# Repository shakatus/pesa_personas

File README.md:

# pesa_personas
Basculas pesa personas

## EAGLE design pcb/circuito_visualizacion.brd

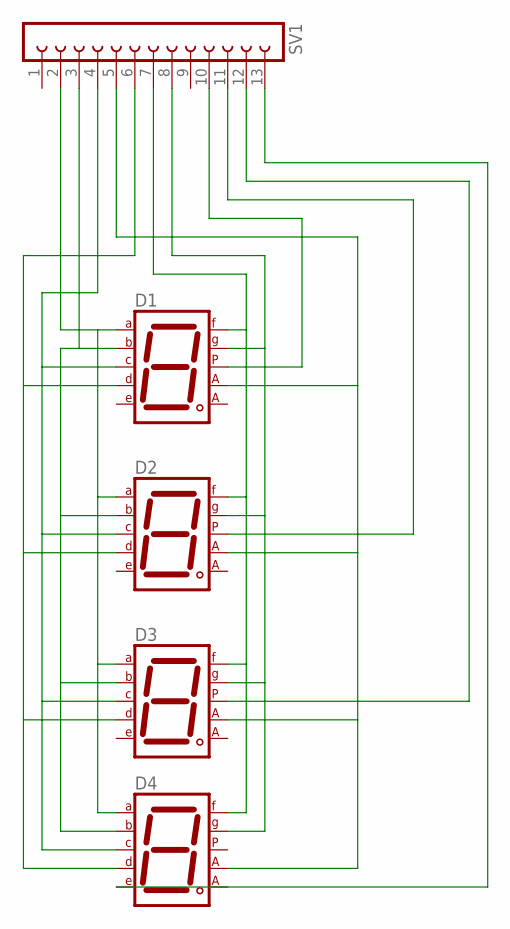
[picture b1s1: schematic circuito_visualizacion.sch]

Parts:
D1, D2, D3, D4: 7SEG-CA; 7SEG-13
SV1: FE13-1; FE13

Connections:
unnamed: D3.5 (DP), SV1.12
unnamed: D4.1 (E), SV1.13
unnamed: D1.5 (DP), SV1.10
unnamed: D1.7 (A), D2.7 (A), D3.7 (A), D4.7 (A), SV1.2
unnamed: D1.6 (B), D2.6 (B), D3.6 (B), D4.6 (B), SV1.3
unnamed: D1.4 (C), D2.4 (C), D3.4 (C), D4.4 (C), SV1.4
unnamed: D1.2 (D), D2.2 (D), D3.2 (D), D4.2 (D), SV1.6
unnamed: D1.9 (F), D2.9 (F), D3.9 (F), D4.9 (F), SV1.7
unnamed: D1.10 (G), D2.10 (G), D3.10 (G), D4.10 (G), SV1.8
unnamed: D2.5 (DP), SV1.11
unnamed: D1.3 (CA1), D2.3 (CA1), D3.3 (CA1), D4.3 (CA1), SV1.5

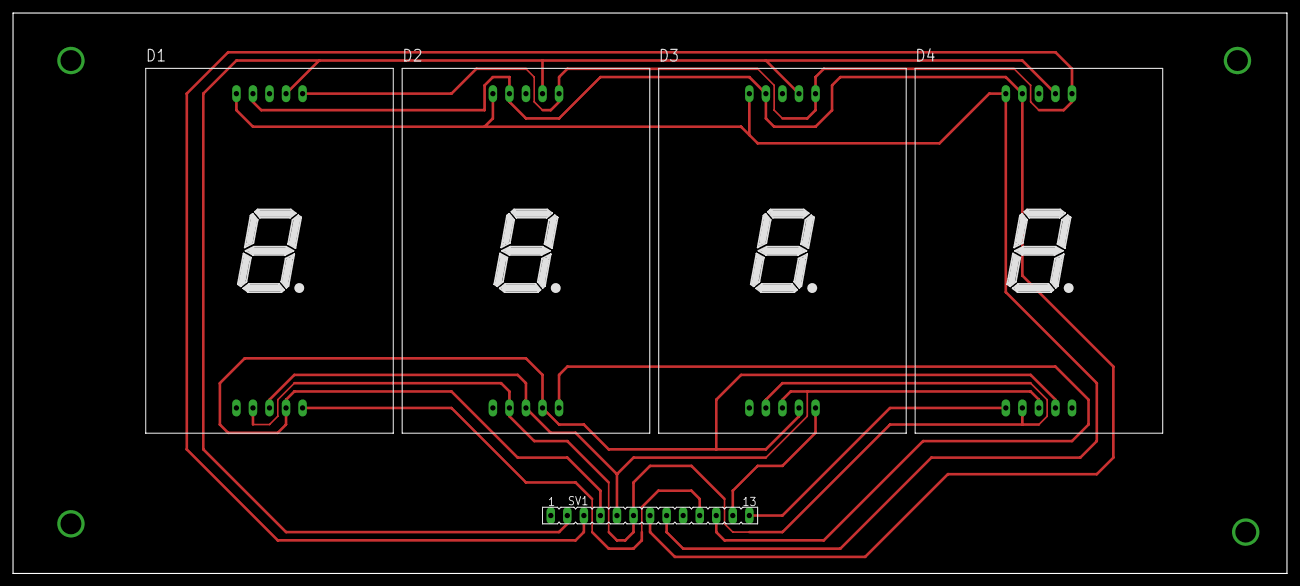
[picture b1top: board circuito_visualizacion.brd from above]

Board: 2 copper layers, 195.6 x 86.0 mm, 5 parts (0 on the bottom side), 11 nets.

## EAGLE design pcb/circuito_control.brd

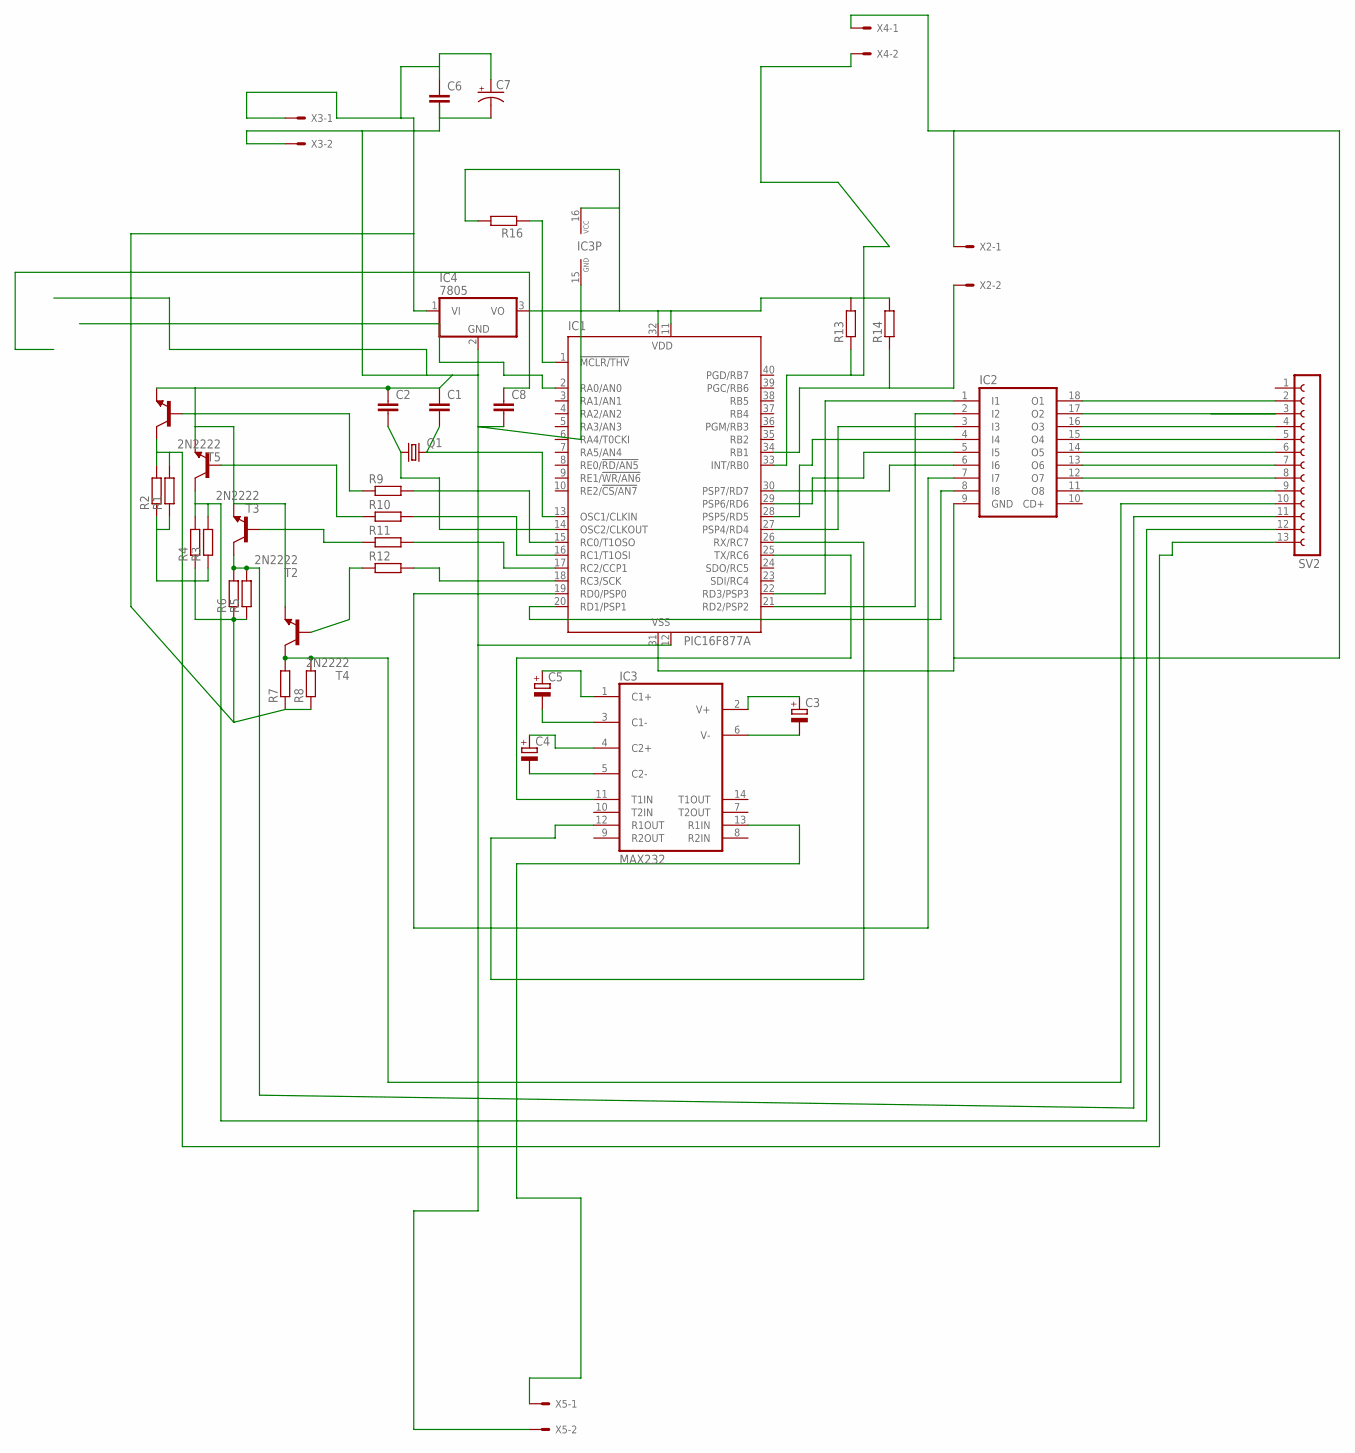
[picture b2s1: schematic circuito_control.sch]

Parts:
C1, C2, C6, C8: C-EU025-025X050; C025-025X050
C3, C4, C5: CPOL-EUE1.8-4; E1,8-4
C7: CPOL-USE5-10.5; E5-10,5
IC1: PIC16F877A; DIL40
IC2: ULN2803A; DIL18
IC3: MAX232; DIL16
IC4: 7805; TO220V
Q1: CRYSTALHC49U70; HC49U70
R1, R2, R3, R4, R5, R6, R7, R8: R-EU_0411/15; 0411/15
R9, R10, R11, R12, R13, R14, R16: R-EU_0207/7; 0207/7
SV2: FE13-1; FE13
T2, T3, T4, T5: 2N2222; TO18
X2, X3, X4, X5: KK-156-2

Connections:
unnamed: C6.1, C7.+, IC4.1 (VI), R1.1, R2.1, R3.1, R4.1, R5.1, R6.1, R7.1, R8.1, X3.1
unnamed: IC1.1 (!MCLR/THV), R16.1
unnamed: IC3.13 (R1IN), X5.1
unnamed: C3.-, IC3.6 (V-)
unnamed: C3.+, IC3.2 (V+)
unnamed: C4.+, IC3.4 (C2+)
unnamed: C4.-, IC3.5 (C2-)
unnamed: C5.-, IC3.3 (C1-)
unnamed: C5.+, IC3.1 (C1+)
unnamed: IC1.25 (TX/RC6), IC3.11 (T1IN)
unnamed: IC1.26 (RX/RC7), IC3.12 (R1OUT)
unnamed: IC1.22 (RD3/PSP3), IC2.1 (I1)
unnamed: IC1.21 (RD2/PSP2), IC2.2 (I2)
unnamed: IC1.28 (PSP5/RD5), IC2.4 (I4)
unnamed: IC1.20 (RD1/PSP1), IC2.8 (I8)
unnamed: IC1.29 (PSP6/RD6), IC2.5 (I5)
unnamed: IC1.30 (PSP7/RD7), IC2.6 (I6)
unnamed: IC1.27 (PSP4/RD4), IC2.3 (I3)
unnamed: IC1.15 (RC0/T1OSO), R9.2
unnamed: IC1.16 (RC1/T1OSI), R10.2
unnamed: IC1.17 (RC2/CCP1), R11.2
unnamed: IC1.18 (RC3/SCK), R12.2
unnamed: R9.1, T5.2 (B)
unnamed: R10.1, T3.2 (B)
unnamed: R11.1, T2.2 (B)
unnamed: R12.1, T4.2 (B)
unnamed: R7.2, R8.2, SV2.10, T4.3 (C)
unnamed: R5.2, R6.2, SV2.11, T2.3 (C)
unnamed: R3.2, R4.2, SV2.12, T3.3 (C)
unnamed: R1.2, R2.2, SV2.13, T5.3 (C)
unnamed: C2.2, IC1.14 (OSC2/CLKOUT), Q1.1
unnamed: IC2.18 (O1), SV2.2
unnamed: IC2.17 (O2), SV2.3
unnamed: IC1.34 (RB1), R14.1, X2.2
unnamed: C8.1, IC1.11 (VDD), IC1.32 (VDD), IC3.16 (VCC), IC4.3 (VO), R13.2, R14.2, R16.2
unnamed: C1.2, IC1.13 (OSC1/CLKIN), Q1.2
unnamed: IC2.16 (O3), SV2.4
unnamed: IC2.15 (O4), SV2.5
unnamed: IC2.14 (O5), SV2.6
unnamed: IC2.13 (O6), SV2.7
unnamed: IC2.12 (O7), SV2.8
unnamed: IC2.11 (O8), SV2.9
unnamed: IC1.33 (INT/RB0), R13.1, X4.2
unnamed: C1.1, C2.1, C6.2, C7.-, C8.2, IC1.12 (VSS), IC1.31 (VSS), IC2.9 (GND), IC3.15 (GND), IC4.2 (GND), T2.1 (E), T3.1 (E), T4.1 (E), T5.1 (E), X2.1, X3.2, X4.1, X5.2
unnamed: IC1.19 (RD0/PSP0), IC2.7 (I7)

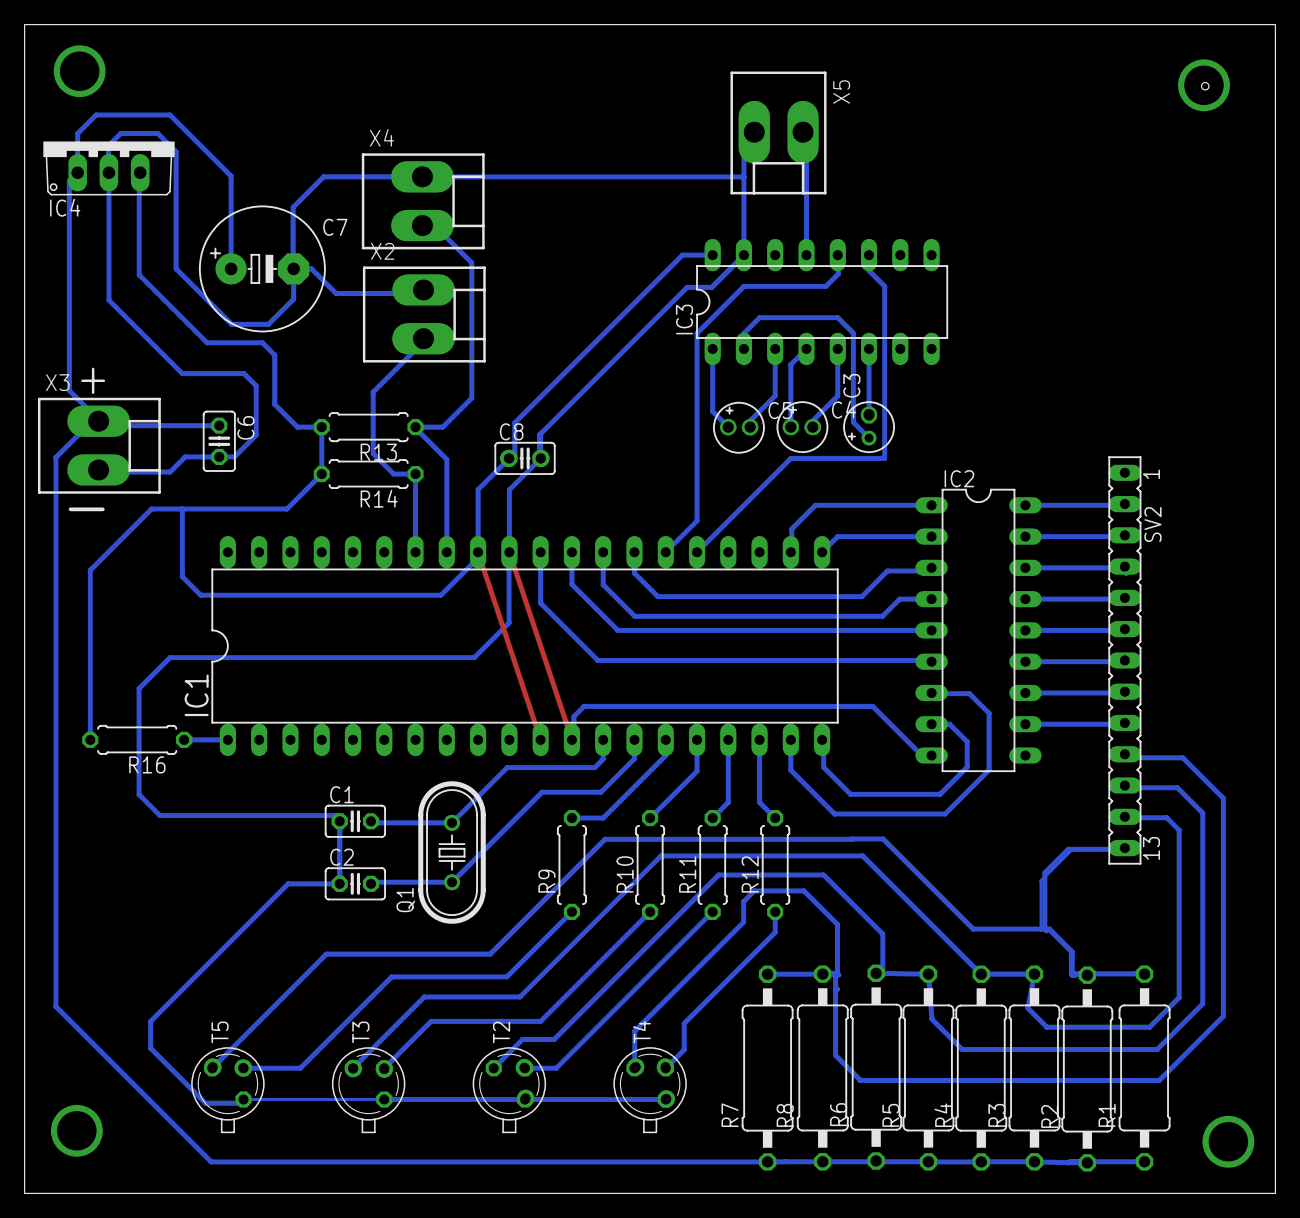
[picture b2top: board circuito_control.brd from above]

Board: 2 copper layers, 101.6 x 94.9 mm, 37 parts (0 on the bottom side), 45 nets.

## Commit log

2015-06-01 :boom::camel: Added .gitattributes & .gitignore files
2015-06-01 Revert ":boom::camel: Added .gitattributes & .gitignore files"
    This reverts commit aa08347a444fd4ab994661be6fdc0066404b9f27.
2015-06-01 prueba
